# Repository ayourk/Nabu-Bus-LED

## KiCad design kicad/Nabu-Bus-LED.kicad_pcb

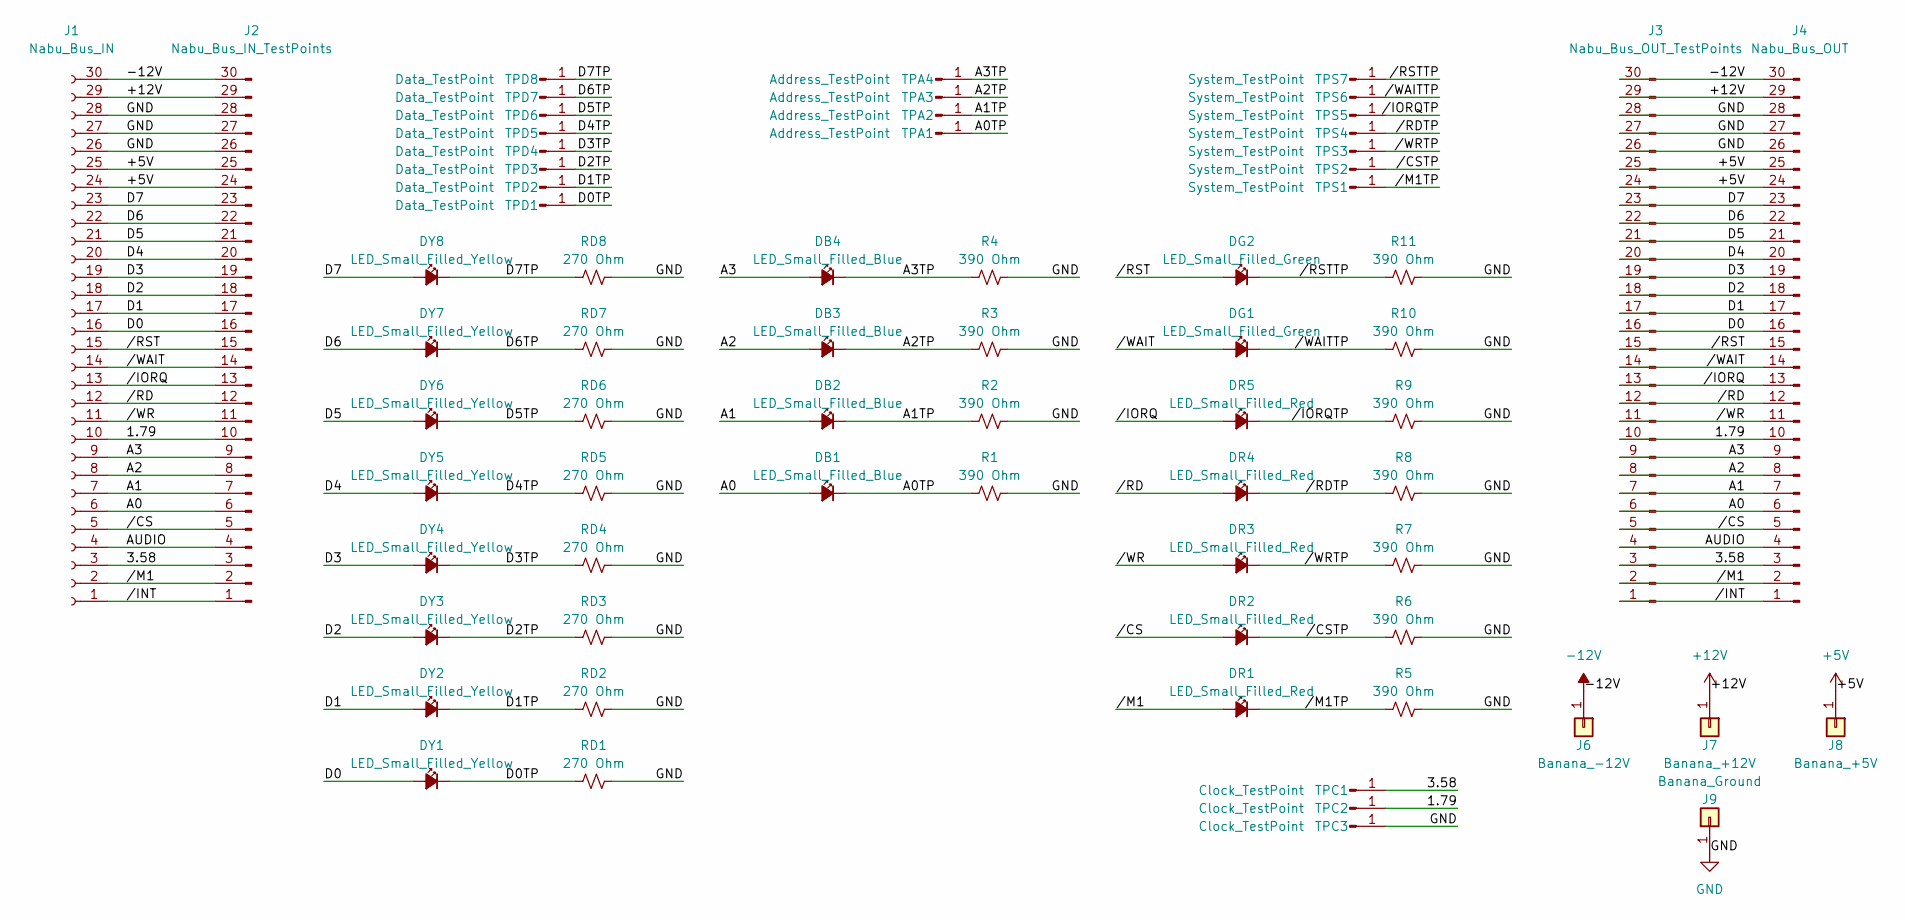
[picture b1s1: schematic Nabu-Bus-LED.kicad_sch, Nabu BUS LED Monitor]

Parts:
DB1, DB2, DB3, DB4: LED_Small_Filled_Blue; LED_1206_3216Metric_Pad1.42x1.75mm_HandSolder; MPN XL-3216UBC; LCSC C965827
DG1, DG2: LED_Small_Filled_Green; LED_1206_3216Metric_Pad1.42x1.75mm_HandSolder; MPN XL-3216UGC; LCSC C965825
DR1, DR2, DR3, DR4, DR5: LED_Small_Filled_Red; LED_1206_3216Metric_Pad1.42x1.75mm_HandSolder; MPN XL-3216SURC; LCSC C965822
DY1, DY2, DY3, DY4, DY5, DY6, DY7, DY8: LED_Small_Filled_Yellow; LED_1206_3216Metric_Pad1.42x1.75mm_HandSolder; MPN XL-3216UYC; LCSC C965824
J1: Nabu_Bus_IN; PinSocket_1x30_P2.54mm_Vertical; MPN SSW-130-22-G-S-RA; Digi-Key_PN SSW-130-22-G-S-RA-ND
J2: Nabu_Bus_IN_TestPoints; PinHeader_1x30_P2.54mm_Vertical; MPN TSW-130-14-T-S; Digi-Key_PN SAM1059-30-ND
J3: Nabu_Bus_OUT_TestPoints; PinHeader_1x30_P2.54mm_Vertical; MPN TSW-130-14-T-S; Digi-Key_PN SAM1059-30-ND
J4: Nabu_Bus_OUT; PinHeader_1x30_P2.54mm_Vertical; MPN TSW-130-25-T-S-RA; Digi-Key_PN 612-TSW-130-25-T-S-RA-ND
J6: Banana_-12V; MountingHole_3.7mm_Banana; MPN 7007; Digi-Key_PN 36-7007-ND
J7: Banana_+12V; MountingHole_3.7mm_Banana; MPN 7006; Digi-Key_PN 36-7006-ND
J8: Banana_+5V; MountingHole_3.7mm_Banana; MPN 7006; Digi-Key_PN 36-7006-ND
J9: Banana_Ground; MountingHole_3.7mm_Banana; MPN 7007; Digi-Key_PN 36-7007-ND
R1, R2, R3, R4, R5, R6, R7, R8, R9, R10, R11: 390 Ohm; R_0805_2012Metric_Pad1.20x1.40mm_HandSolder; MPN ERJ-6ENF3900V; Digi-Key_PN P390CCT-ND
RD1, RD2, RD3, RD4, RD5, RD6, RD7, RD8: 270 Ohm; R_0805_2012Metric_Pad1.20x1.40mm_HandSolder; MPN ERJ-6ENF2700V; Digi-Key_PN P270CCT-ND
TPA1, TPA2, TPA3, TPA4: Address_TestPoint; TestPoint_Pad_SMD_1206; MPN RCW-0C; Digi-Key_PN A106146CT-ND
TPC1, TPC2, TPC3: Clock_TestPoint; TestPoint_Pad_SMD_1206; MPN RCW-0C; Digi-Key_PN A106146CT-ND
TPD1, TPD2, TPD3, TPD4, TPD5, TPD6, TPD7, TPD8: Data_TestPoint; TestPoint_Pad_SMD_1206; MPN RCW-0C; Digi-Key_PN A106146CT-ND
TPS1, TPS2, TPS3, TPS4, TPS5, TPS6, TPS7: System_TestPoint; TestPoint_Pad_SMD_1206; MPN RCW-0C; Digi-Key_PN A106146CT-ND

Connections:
+5V: J1.24, J1.25, J2.24, J2.25, J3.24, J3.25, J4.24, J4.25, J8.1
+12V: J1.29, J2.29, J3.29, J4.29, J7.1
-12V: J1.30, J2.30, J3.30, J4.30, J6.1
/1.79: J1.10, J2.10, J3.10, J4.10, TPC2.1
/3.58: J1.3, J2.3, J3.3, J4.3, TPC1.1
/A0: DB1.2 (A), J1.6, J2.6, J3.6, J4.6
/A0TP: DB1.1 (K), R1.1, TPA1.1
/A1: DB2.2 (A), J1.7, J2.7, J3.7, J4.7
/A1TP: DB2.1 (K), R2.1, TPA2.1
/A2: DB3.2 (A), J1.8, J2.8, J3.8, J4.8
/A2TP: DB3.1 (K), R3.1, TPA3.1
/A3: DB4.2 (A), J1.9, J2.9, J3.9, J4.9
/A3TP: DB4.1 (K), R4.1, TPA4.1
/AUDIO: J1.4, J2.4, J3.4, J4.4
/D0: DY1.2 (A), J1.16, J2.16, J3.16, J4.16
/D0TP: DY1.1 (K), RD1.1, TPD1.1
/D1: DY2.2 (A), J1.17, J2.17, J3.17, J4.17
/D1TP: DY2.1 (K), RD2.1, TPD2.1
/D2: DY3.2 (A), J1.18, J2.18, J3.18, J4.18
/D2TP: DY3.1 (K), RD3.1, TPD3.1
/D3: DY4.2 (A), J1.19, J2.19, J3.19, J4.19
/D3TP: DY4.1 (K), RD4.1, TPD4.1
/D4: DY5.2 (A), J1.20, J2.20, J3.20, J4.20
/D4TP: DY5.1 (K), RD5.1, TPD5.1
/D5: DY6.2 (A), J1.21, J2.21, J3.21, J4.21
/D5TP: DY6.1 (K), RD6.1, TPD6.1
/D6: DY7.2 (A), J1.22, J2.22, J3.22, J4.22
/D6TP: DY7.1 (K), RD7.1, TPD7.1
/D7: DY8.2 (A), J1.23, J2.23, J3.23, J4.23
/D7TP: DY8.1 (K), RD8.1, TPD8.1
//CS: DR2.2 (A), J1.5, J2.5, J3.5, J4.5
//CSTP: DR2.1 (K), R6.1, TPS2.1
//INT: J1.1, J2.1, J3.1, J4.1
//IORQ: DR5.2 (A), J1.13, J2.13, J3.13, J4.13
//IORQTP: DR5.1 (K), R9.1, TPS5.1
//M1: DR1.2 (A), J1.2, J2.2, J3.2, J4.2
//M1TP: DR1.1 (K), R5.1, TPS1.1
//RD: DR4.2 (A), J1.12, J2.12, J3.12, J4.12
//RDTP: DR4.1 (K), R8.1, TPS4.1
//RST: DG2.2 (A), J1.15, J2.15, J3.15, J4.15
//RSTTP: DG2.1 (K), R11.1, TPS7.1
//WAIT: DG1.2 (A), J1.14, J2.14, J3.14, J4.14
//WAITTP: DG1.1 (K), R10.1, TPS6.1
//WR: DR3.2 (A), J1.11, J2.11, J3.11, J4.11
//WRTP: DR3.1 (K), R7.1, TPS3.1
GND: J1.26, J1.27, J1.28, J2.26, J2.27, J2.28, J3.26, J3.27, J3.28, J4.26, J4.27, J4.28, J9.1, R1.2, R2.2, R3.2, R4.2, R5.2, R6.2, R7.2, R8.2, R9.2, R10.2, R11.2, RD1.2, RD2.2, RD3.2, RD4.2, RD5.2, RD6.2, RD7.2, RD8.2, TPC3.1

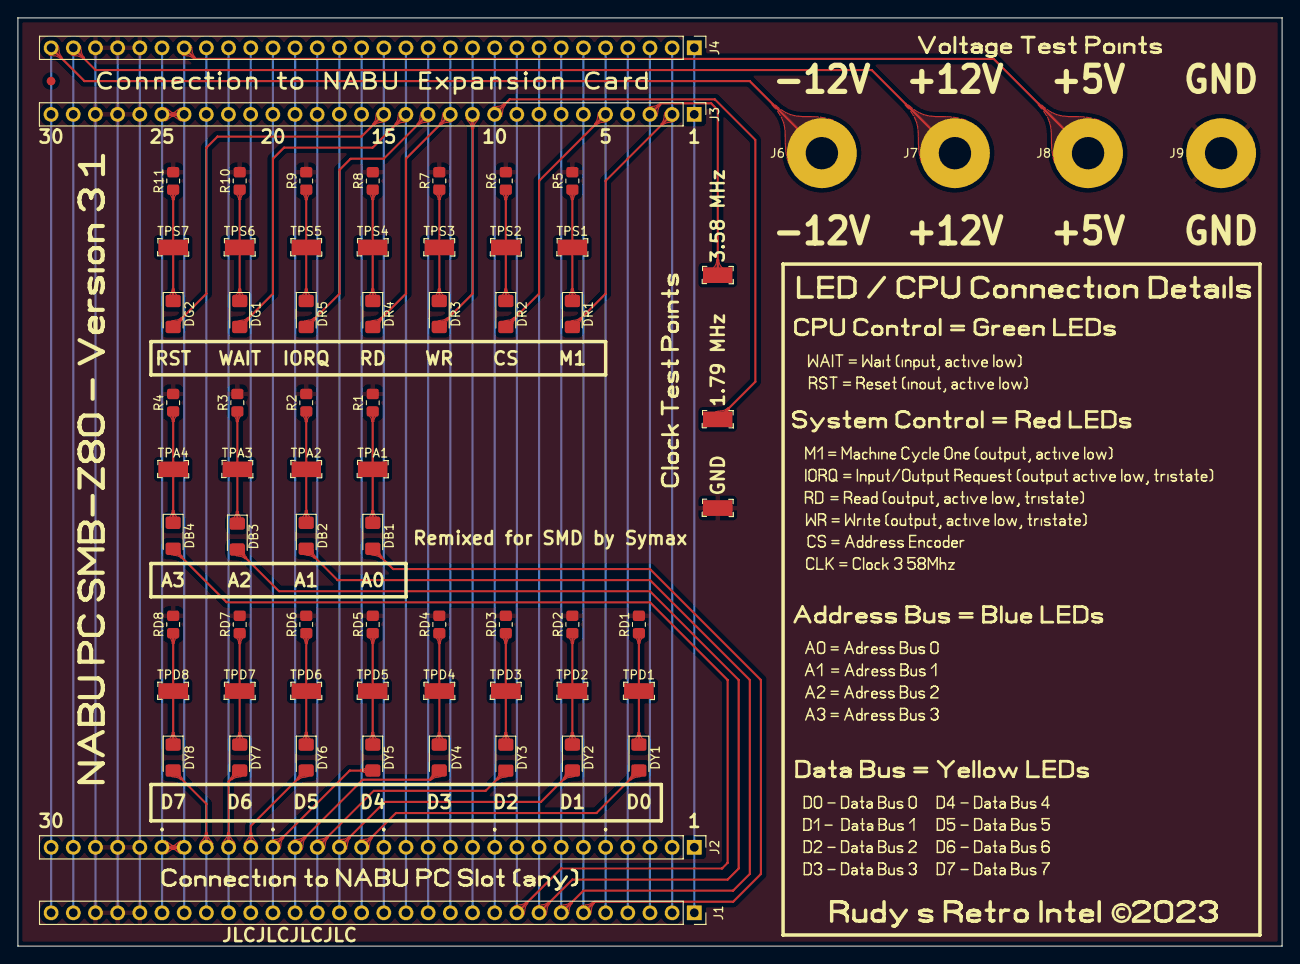
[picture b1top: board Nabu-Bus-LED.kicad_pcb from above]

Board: 2 copper layers, 144.8 x 106.3 mm, 69 parts (0 on the bottom side), 46 nets.

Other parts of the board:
REF01: Fiducial_1mm_Mask2mm

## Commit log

2023-07-17 Converted the Gerbers to a full Kicad 6.0.x project.
2023-07-17 Moved Clock Test points to more closely match PCB location.
2023-07-17 Add HTML BOM to project.
2023-07-25 Added "Remixed by Symax" label.
